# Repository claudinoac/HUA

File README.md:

# HUA é um projeto de horta urbana automatizada que une irrigação automatizada ao reuso de materiais, incentivando e ajudando o cultivo domiciliar de alimentos.

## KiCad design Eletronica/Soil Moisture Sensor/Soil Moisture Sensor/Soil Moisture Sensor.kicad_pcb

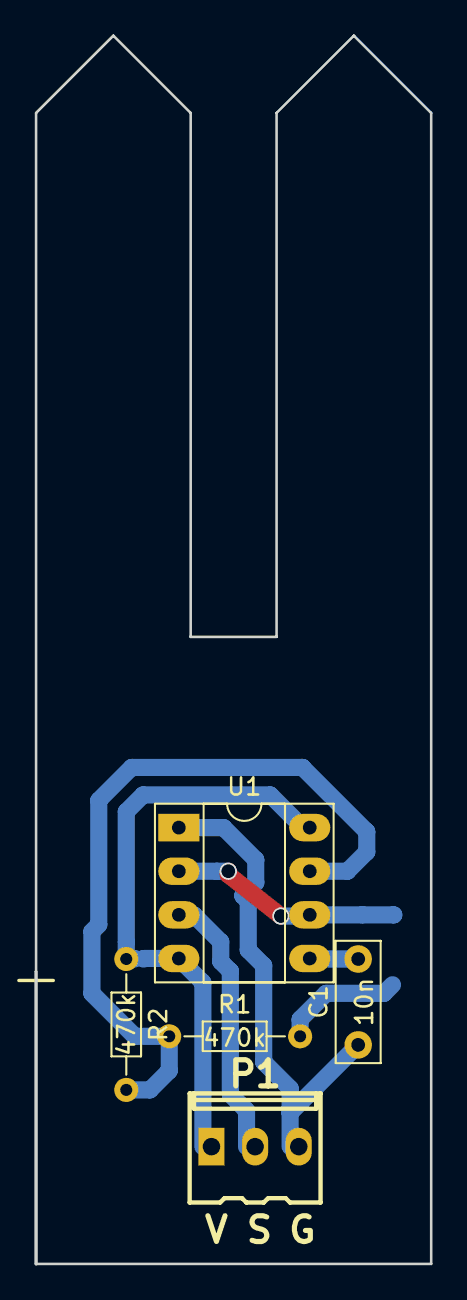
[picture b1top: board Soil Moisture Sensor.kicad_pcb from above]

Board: 2 copper layers, 23.0 x 71.5 mm, 5 parts (0 on the bottom side), 6 nets.

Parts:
C1: 10n; C_Rect_L7.0mm_W2.5mm_P5.00mm
P1: OUT; kk100_22-23-2031
R1, R2: 470k; R_Axial_DIN0204_L3.6mm_D1.6mm_P7.62mm_Horizontal
U1: NE555; DIP-8_W7.62mm_Socket_LongPads

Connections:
+5V: P1.1, R2.1, U1.4, U1.8
GND: C1.1, P1.3, U1.1
unnamed: C1.2, U1.5
unnamed: R1.1, R2.2, U1.7
SENS1: R1.2, U1.2, U1.6
SGN: P1.2, U1.3

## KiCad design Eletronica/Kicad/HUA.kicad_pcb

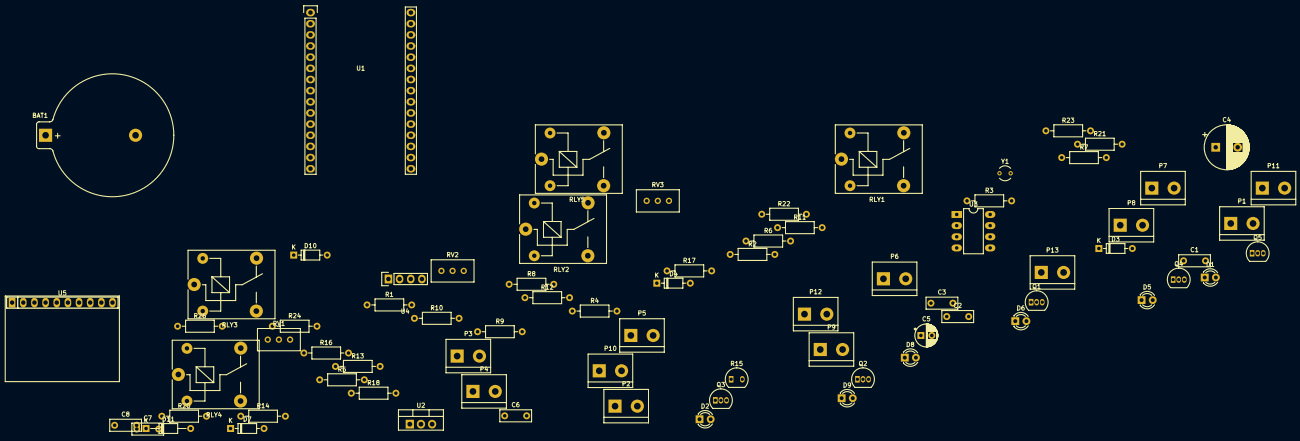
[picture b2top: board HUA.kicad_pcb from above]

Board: 2 copper layers, 76 parts (0 on the bottom side), 55 nets, no tracks yet.

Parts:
BAT1: BAT; BatteryHolder_Keystone_106_1x20mm
C1, C2, C3, C6, C7, C8: 100n; C_Rect_L7.0mm_W2.5mm_P5.00mm
C4: 100u; CP_Radial_D10.0mm_P5.00mm
C5: 10u; CP_Radial_D5.0mm_P2.50mm
D1, D2, D6, D8, D9: 3mm; LED_D3.0mm_Clear
D3, D4, D7, D10: 1N4001; D_DO-35_SOD27_P7.62mm_Horizontal
D5: PWR_LED; LED_D3.0mm
D11: 1N4001; D_DO-35_SOD27_P10.16mm_Horizontal
P1: EXT_V1; TerminalBlock_bornier-2_P5.08mm
P2: VALV_1; TerminalBlock_bornier-2_P5.08mm
P3: EXT_RL1; TerminalBlock_bornier-2_P5.08mm
P4: RL_1; TerminalBlock_bornier-2_P5.08mm
P5: EXT_V2; TerminalBlock_bornier-2_P5.08mm
P6: VALV_2; TerminalBlock_bornier-2_P5.08mm
P7: EXT_RL2; TerminalBlock_bornier-2_P5.08mm
P8: RL_2; TerminalBlock_bornier-2_P5.08mm
P9: EXT_V3; TerminalBlock_bornier-2_P5.08mm
P10: VALV_3; TerminalBlock_bornier-2_P5.08mm
P11: HUM1_SENSOR; TerminalBlock_bornier-2_P5.08mm
P12, P13: HUM2_SENSOR; TerminalBlock_bornier-2_P5.08mm
Q1, Q2, Q3, Q4, Q5: BC546; TO-92_Inline
R1, R2, R5, R6, R8, R9, R12, R13, R17, R18, R22, R23, R24, R26: 1k; R_Axial_DIN0207_L6.3mm_D2.5mm_P10.16mm_Horizontal
R3, R4, R7, R10, R11: 2k7; R_Axial_DIN0207_L6.3mm_D2.5mm_P10.16mm_Horizontal
R14: 20k; R_Axial_DIN0207_L6.3mm_D2.5mm_P10.16mm_Horizontal
R15: LDR; TO-92-2
R16, R20, R21: 100k; R_Axial_DIN0207_L6.3mm_D2.5mm_P10.16mm_Horizontal
RLY1, RLY2, RLY3, RLY4, RLY5: RELAY_HJR-3FF_Z; Relay_SPDT_SANYOU_SRD_Series_Form_C
RV1, RV2, RV3: 20k; Potentiometer_Bourns_3296W_Vertical
U1: NodeMCU_Amica_R2
U2: LM7805CT; TO-220-3_Vertical
U3: DS1307+; DIP-8_W7.62mm_LongPads
U4: DHT22; DHT22_Temperature_Humidity
U5: ADS1115
Y1: Crystal_Small; Crystal_AT310_D3.0mm_L10.0mm_Vertical

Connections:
+3V3: BAT1.1, R12.1, R13.1, R14.1, R18.2, R24.2, R26.2, U1.11, U1.16, U1.25, U3.3, U3.8, U4.1, U5.1
+5V: C5.1, C6.1, U1.15, U2.3
+12V: C4.1, D3.1, D4.1, D7.1, D10.1, D11.1, R3.1, R4.1, R6.1, R7.1, R10.1, R11.1, RLY1.5, RLY2.5, RLY3.5, RLY4.5, RLY5.5, U2.1
DHT: U1.20, U4.2
GND: BAT1.2, C1.2, C2.2, C3.2, C4.2, C5.2, C6.2, C7.2, C8.2, D5.1, Q1.3, Q2.3, Q3.3, Q4.3, Q5.3, R15.2, R16.1, R20.1, R21.1, U1.14, U1.17, U1.24, U2.2, U3.4, U4.4, U5.2, U5.5
HUM1_IN: R16.2, R17.2, U1.23, U5.9
HUM2_IN: R20.2, R22.2, U1.22, U5.8
HUM3_IN: R21.2, R23.2, U1.21, U5.7
LDR: R14.2, R15.1, U5.10
unnamed: C1.1, Q1.2, R1.1
unnamed: C2.1, Q2.2, R2.1
unnamed: C3.1, Q3.2, R5.1
unnamed: C7.1, Q4.2, R8.1
unnamed: C8.1, Q5.2, R9.1
unnamed: D1.1, D3.2, Q1.1, RLY1.2
unnamed: D1.2, R3.2
unnamed: D2.1, D4.2, Q2.1, RLY2.2
unnamed: D2.2, R4.2
unnamed: D5.2, R6.2
unnamed: D6.1, D7.2, Q3.1, RLY3.2
unnamed: D6.2, R7.2
unnamed: D8.2, R10.2
unnamed: D9.2, R11.2
unnamed: D8.1, D10.2, Q4.1, RLY4.2
unnamed: D9.1, D11.2, Q5.1, RLY5.2
unnamed: P1.1, RLY1.4
unnamed: P1.2, P2.1
unnamed: P2.2, RLY1.1
unnamed: P3.1, RLY2.4
unnamed: P3.2, P4.1
unnamed: P4.2, RLY2.1
unnamed: P5.1, RLY3.4
unnamed: P5.2, P6.1
unnamed: P6.2, RLY3.1
unnamed: P7.1, RLY4.4
unnamed: P7.2, P8.1
unnamed: P8.2, RLY4.1
unnamed: P9.1, RLY5.4
unnamed: P9.2, P10.1
unnamed: P10.2, RLY5.1
unnamed: P11.1, R18.1, RV1.1
unnamed: P11.2, R17.1, RV1.2, RV1.3
unnamed: P12.1, R24.1, RV2.1
unnamed: P12.2, R22.1, RV2.2, RV2.3
unnamed: P13.1, R26.1, RV3.1
unnamed: P13.2, R23.1, RV3.2, RV3.3
unnamed: U3.1, Y1.1
unnamed: U3.2, Y1.2
RL1: R2.2, U1.30
RL2: R8.2, U1.29
SCL: R12.2, U1.4, U3.6, U5.3
SDA: R13.2, U1.5, U3.5, U5.4
VALV1: R1.2, U1.26
VALV2: R5.2, U1.27
VALV3: R9.2, U1.28

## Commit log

2017-08-19 eletronica
2017-10-03 Add files via upload
    Esquema Fritzing de montagem de protoboard com medidor de umidade do solo usando monitor LCD, Potenciometro e um LED.
2017-12-11 Rename esqUmidSolo_fundino_led_LCD.ino to esqUmidSoloDESIGNRIO
2017-12-12 Add files via upload
    Aqui você encontra a programação usada no medidor de umidade do solo para a oficina HUA da PLASTCOLAB
2017-12-12 oficina HUA - PLASTCOLAB
    oficina HUA - PLASTCOLAB
    imagem esquemática de como deve ser montado o sistema para medidor de umidade do solo.
2018-04-10 Kicad SCH of Version 0.1
2018-04-12 ADD: Bill of Materials
2018-12-04 EDIT: NODEMCU as a replacement for arduino (V2)
2018-12-05 ADD: Soil Moisture Sensor circuit and Fabrication Files
2018-12-05 ADD: Soil Moisture Sensor's G-Codes
2018-12-06 EDIT: Soil Moisture Sensor's G-Codes for PCB Milling
2021-10-10 [HUA-001] refactor: move electronics and BOM files to proper directory
2021-10-10 feat: create arduino uno code in rust
